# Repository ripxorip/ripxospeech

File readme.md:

# Ripxovoice

## Description

This readme is a WIP.

## Getting Started

### Dependencies

List any dependencies that need to be installed for this software to work. For example:

- Dependency 1
- Dependency 2

### Setup

(2024/01/07) This way of connecting everything is now deprecated. I am now using physical USB audio interfaces that gets passthrough to each virtual machine. This way I have a lot simpler streaming setup as I only need to stream from my workstation to a node which feeds line level audio to each audio interface.The next step is to create a desktop application which manages the actual part that runs on the workstation, unifying both the audio streaming and managing how keystrokes gets sent. Some current ideas I have includes:

- Being able to switch between English and Swedish using a button in a GUI.
    - Done by the workstation figuring out if Windows is in English or Swedish mode currently using a screenshot or something similar.

Currently (2023/12/17) setup everything accordingly:
(Note: There is no longer any need for running the audio from the VM host, voiceboxlinux also manages the routing to Windows using 192.168.122.xxx)

- In voiceboxlinux start Jacktrip: `PIPEWIRE_LATENCY="1024/48000" jacktrip -s`
- In Windows:
    - Start qjackctl (Pinned on the taskbar)
- In Windows:
    - Start Jacktrip (from terminal): `.\jacktrip.exe -c 192.168.122.137`
- In voiceboxlinux start the server: `./linux_gstreamer_server/serve_dest.sh`
- Route audio from client (can be any client)
- In voiceboxlinux Manually route the audio according to this screenshot: 

## TODOs
- Update this readme..
- I have decided to not use Linux for the Talon slave, consequently I am going to use Windows for that as well.
  The next step is to be able to get those keyboard events from the same application which is currently being
  used to fetch the keyboard strokes from Windows 11 own speech to text service. This application is called
  win11_keysender and it is written in C#.

### Using

Instructions for how to use your project. For example:

- Step 1
- Step 2

## Contributing

Details about how other developers can contribute to your project.

## License

Information about the license your project uses.

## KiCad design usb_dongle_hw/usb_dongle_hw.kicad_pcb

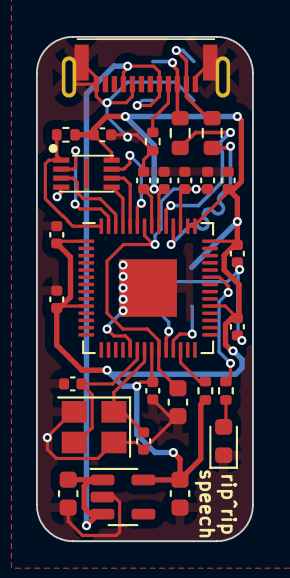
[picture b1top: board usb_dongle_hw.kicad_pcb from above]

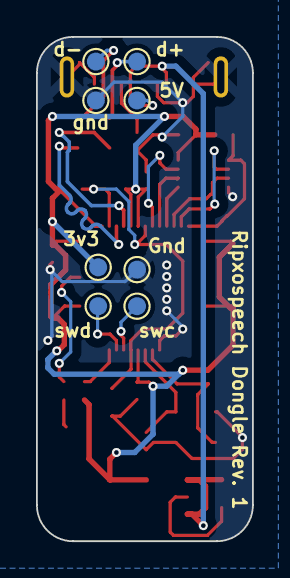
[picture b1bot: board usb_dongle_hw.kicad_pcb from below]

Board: 2 copper layers, 12.0 x 28.0 mm, 36 parts (8 on the bottom side), 22 nets.

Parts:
C1, C2: 12p; C_0402_1005Metric
C3, C5, C6, C7, C8, C9, C10, C11, C12, C13, C14: 0.1u; C_0402_1005Metric
C4: 1u; C_0603_1608Metric
C15, C16: 10uF; C_0603_1608Metric
D1: Blue; LED_0603_1608Metric
J1: PLUG-USBC-121SMT-4BS2S
R1: 1K; R_0402_1005Metric
R2: 470; R_0402_1005Metric
R3: 10K; R_0402_1005Metric
R4: 5.1k; R_0402_1005Metric
R5, R6: 27; R_0603_1608Metric
TP1, TP2, TP3, TP4, TP5, TP6, TP7, TP8: TestPoint; TestPoint_Pad_D1.0mm
U1: RP2040; QFN-56-1EP_7x7mm_P0.4mm_EP3.2x3.2mm
U2: W25Q64JV; SON50P300X200X60-9N
U3: AP2112K-3.3; SOT-23-5
Y1: 12Mhz; Crystal_SMD_3225-4Pin_3.2x2.5mm

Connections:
+1V1: C3.1, C4.1, C5.1, U1.23 (DVDD), U1.45 (VREG_VOUT), U1.50 (DVDD)
+3V3: C6.1, C7.1, C8.1, C9.1, C10.1, C11.1, C12.1, C13.1, C14.1, C16.1, R1.1, R3.2, TP1.1, U1.1 (IOVDD), U1.10 (IOVDD), U1.22 (IOVDD), U1.33 (IOVDD), U1.42 (IOVDD), U1.43 (ADC_AVDD), U1.44 (VREG_IN), U1.48 (USB_VDD), U1.49 (IOVDD), U2.8 (VDD), U3.5 (VOUT)
+5V: C15.1, J1.A04, J1.B09, TP7.1, U3.1 (VIN), U3.3 (EN)
/usb-d+: R5.2, U1.47 (USB_D+)
/usb-d-: R6.2, U1.46 (USB_D-)
GND: C1.1, C2.1, C3.2, C4.2, C5.2, C6.2, C7.2, C8.2, C9.2, C10.2, C11.2, C12.2, C13.2, C14.2, C15.2, C16.2, D1.1 (K), J1.A01, J1.A12, J1.B12, J1.Gnd, R4.1, TP2.1, TP8.1, U1.19 (TESTEN), U1.57 (GND), U2.4 (GND), U3.2 (GND), Y1.2, Y1.4
unnamed: D1.2 (A), R2.1
unnamed: J1.A05, R4.2
unnamed: R2.2, U1.37 (GPIO25)
unnamed: R1.2, U1.26 (RUN)
unnamed: C1.2, U1.20 (XIN), Y1.3
unnamed: C2.2, U1.21 (XOUT), Y1.1
QSPI_CS: R3.1, U1.56 (QSPI_SS), U2.1 (~CS)
QSPI_SCLK: U1.52 (QSPI_SCLK), U2.6 (SCK)
QSPI_SD0: U1.53 (QSPI_SD0), U2.5 (DI/IO0)
QSPI_SD1: U1.55 (QSPI_SD1), U2.2 (DO/IO1)
QSPI_SD2: U1.54 (QSPI_SD2), U2.3 (~WP/IO2)
QSPI_SD3: U1.51 (QSPI_SD3), U2.7 (~HOLD/IO3)
SWCLK: TP4.1, U1.24 (SWCLK)
SWDIO: TP3.1, U1.25 (SWD)
USB_d+: J1.A06, R5.1, TP5.1
USB_d-: J1.A07, R6.1, TP6.1

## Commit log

2023-10-20 feat: Initial commit
2023-10-21 feat: Adds pip reqs
2023-10-21 feat: Adds table to translate the xev keycodes to name
2023-10-22 feat: Adds translation to HID report, next up colemak translation
2023-10-22 feat: Adds initial function to convert keycodes to colemak dh
2023-10-22 feat: Adds initial version of the key_presser class, managed to get some keys pressed (full chain using aplay instead of a soundcard though)
2023-10-22 fix: Colemak mappings
2023-10-22 Adds support for modifier keys
2023-10-24 feat: Adds setup/teardown script for pipewire pipeline
2023-10-27 feat: Changes from http to raw UDP sockets
2023-10-27 feat: removes flask
2023-10-27 wip: Scripting refactoring
2023-10-27 feat: Adds support for switching using a script
2023-10-27 fix: removes not needed scripts
2023-11-03 feat: Disables pulseaudio native module, will use gstreamer instead
2023-11-03 fix: Syntax error
2023-11-03 feat: WIP for python script for routing
2023-11-08 feat: Tmux seems promising
2023-11-09 feat: Adds support for Gstreamer accelerated talon
2023-11-10 feat: Pulse/pipewire routing for Windows VM (neet to tune latency somewhere)
2023-11-12 feat: Adds support for sending text messages from run.py (fk route.py)
2023-11-12 fix: Param not needed anymore
2023-11-12 fix: Naming
2023-11-13 feat: Adds python script which sends to clipboard, (dummy solution)
2023-11-13 wip: Win11 + testing
2023-11-14 feat: Unified stream for both backends
2023-11-14 feat: Adds support for sending strings to the ripxovoice devices
2023-11-14 feat: Adds support for client to read HID data
2023-11-15 wip: HID commands
2023-11-16 feat: Adds the rest of the HID commands
2023-11-16 feat: Client HID commands
2023-11-17 fix: typo
2023-11-25 feat: Consolidation with the other two project
2023-11-25 feat: Initial commit for the OCR stuff
2023-11-25 feat: Adds polling
2023-11-25 feat: Focus the application when starting dictation
2023-11-25 feat: OCR reacts to data on 5005
2023-11-25 feat: Adds HID for gdocs
2023-11-25 HID on client as well
2023-11-25 feat: Ready for actual logic (see Form1.cs)
2023-11-27 fix: Not needed files
2023-11-27 feat: First working version
2023-12-01 feat: Adds Gstreamer Server for Windows
2023-12-01 chore: Renaming
2023-12-01 feat: Queues and not killing servers
2023-12-01 Update the gst path for Win
2023-12-01 fix: Win ip
2023-12-01 fix: Temporarily disable Linux app switching, bug?
2023-12-01 feat: Adds python script for routing, might be needed when tear down not working on windows
2023-12-02 feat: Refactoring to ripxospeech.py instead of run.py
2023-12-02 chore: more refactoring
2023-12-02 chore: first part of the refactoring of the server
2023-12-02 chore: continued refactoring to enable more backends for sending the keystrokes
2023-12-02 chore: more refectoring
2023-12-02 feat: add to support so that the dictation is automatically stopped when changing language
2023-12-02 chore: refactored away that part that has to do with commands from the keyboard server
2023-12-07 feat: Gst server from python + flake
2023-12-08 feat: Adds win11 pcm scaffolding
2023-12-08 feat: Adds support for vscode build
2023-12-08 feat: VSCode task for server and python client (needs to be rewritten)
2023-12-08 feat: Task for running the client as well
2023-12-09 feat: New audio setup (gst + jack)
2023-12-09 fix: Env
2023-12-09 fix: Env so that it works on both nix and other distros
2023-12-11 feat: Initial scaffolding with inspiration from the magslide_firmware (controller)
2023-12-14 feat: Add nix derivation for the embedded firmware of the USB dongle
2023-12-16 feat: Adds support for resetting the embedded dongle (send 0x66) and scaffolding for receiving HID data
2023-12-16 feat: add support for flashing the dongle from the main script
2023-12-16 feat: First working version! Need to understand where the latency is coming from, but anyway it works.
2023-12-17 feat: Fixes the latency issues. Ready for review
2023-12-17 feat: Adds support for routing local audio
2023-12-17 Add support for USB dongle (RP2040) (#1)
    * feat: Initial scaffolding with inspiration from the magslide_firmware (controller)
    * feat: Add nix derivation for the embedded firmware of the USB dongle
    * feat: Adds support for resetting the embedded dongle (send 0x66) and scaffolding for receiving HID data
    * feat: add support for flashing the dongle from the main script
    * feat: First working version! Need to understand where the latency is coming from, but anyway it works.
    * feat: Fixes the latency issues. Ready for review
2023-12-17 feat: Add support for blinking the LED when transmitting keyboard strokes from the USB dongle
2023-12-17 feat: voiceboxlinux is now audio master, not ripxolab
2024-01-07 feat: New architecture, pi to pi and sound cards for the VMs
2024-01-07 feat: Updates to read me file to include some ideas I have for the future
2024-01-07 fix: fixes broken key up
2024-01-07 Fixes apostrophe
2024-01-08 feat: Initial commit (build using nix develop nix develop .#ripxospeech_gtk -c $SHELL and start code from there
2024-01-08 feat: Adds my name as dev
2024-01-11 feat: Python instead of C for GUI
2024-01-14 fix: moves silk
2024-01-14 feat: DRC pass, routing complete
2024-01-14 fix: Silk
2024-01-15 feat: This goes into JLCPCB production
2024-01-15 feat: Adds support for starting/stopping the client stream. The same shall be done for the audio server (Rpi) use setsid etc when wrapping to a socket server.
2024-01-16 feat: Adds socket server for starting/stoping the gst server
2024-01-16 feat: Start/stop the gst server when pushing the button
2024-01-16 fix: Proctects against multiple starts
2024-01-16 feat: Adds support for starting/stopping audio stream when a key is pushed from Gnome/Pi
2024-01-16 feat: Style using CSS example
2024-01-16 wip: UI
2024-01-17 feat: GUI Structure
2024-01-17 feat: GUI Makeup
2024-01-17 feat: Buttons connected
2024-01-17 feat: Adds stop button, next step is dongle status and then changing language
2024-01-17 feat: Dongle status
2024-01-17 feat: Clean status text
2024-01-17 feat: Adds convenience script for starting the current GUI
2024-01-17 wip: Win lang switching, will be a screenshot with Python OCR and TCP instead
2024-01-18 feat: Adds support for changing lang
2024-01-18 feat: Able to change Win language using OCR
2024-01-18 fix: Ignored image
2024-01-18 fix: Adds error handling if I get a bad message.
2024-01-19 feat: Adds support for virtual keyboard without any dongles
2024-01-20 chore: Virtual keyboard cleanup
2024-01-21 feat: Adds code server for Talon config
2024-01-21 feat: Open Talon config from GUI, OBS: Im sick as a dog so this and the previous commits needs to be checked when Im back on my feet again
2024-01-22 fix: Commands kept on haning, doing it the python way instead
2024-01-22 fix: send_string to bytes
2024-01-27 feat: Input commands cleanup
2024-01-27 feat: Adds server side support for åä and ö
2024-01-27 feat: Adds fn keys as generic actions rather than hard coded actions (more flexible this way)
2024-01-27 Restarts the app on language switching through the debugger
2024-01-27 feat: Fully working language switching for windows
2024-01-27 feat: Adds Doublethink class for preprocessing, undo/redo and inline editing using voice
2024-01-28 feat: The doublethink can now parse the text and repack it afterwards
2024-01-28 feat: initial, see logseq bugs
2024-01-29 fix: Protect against hidraw not existing, next up gst missing on vanila system
2024-01-29 fix: Adds missing gstreamer
2024-01-30 feat: Proper killing
2024-01-30 wip: Test scaffoliding
2024-03-10 fix: This test clearly proves that there is nothing wrong when sending bursts of messages, rather the error is somewhere in the doublethink code
2024-03-11 WIP: Audio latency test WIP
2024-03-11 feat: First working version of the audio latency test sequence
2024-03-11 feat: Now saves the recording for future reference
2024-03-12 feat: Adds combined stream script
2024-03-20 feat: adds testing script for local raspberry pi
2024-03-30 feat: Initial commit of the gateway, can now stream a sine in realtime
2024-03-31 feat: Async alsa playback
2024-03-31 fix: Cleanup
2024-03-31 feat: Initial commit of the client
2024-04-14 wip: Audio gateway
2024-04-14 wip: audio client
2024-04-14 feat: Test with select instead of separate thread
2024-04-14 feat: First working version, although a bit naive perhaps, need to figure out what happens when loosing sync etc
2024-04-14 fix: Yet another copliot bug
2024-04-15 feat: Adds USB soundcard prober (for finding the master device among the three identical USB dongles)
2024-04-16 feat: XML format for device detection
2024-06-14 feat: Gateway uses pipewire instead
2024-06-14 wip: Working streame on localhost
2024-06-14 Cleanup and adds new sources for the buffer/sync functions
2024-06-14 chore: Removes not needed struct
2024-06-14 feat: Adds unittest
2024-06-14 feat: Test when in sync, next up add a buffer
2024-06-14 feat: Adds ring_buffer
2024-06-14 feat: Adds mutex, shall be used for the ring_buffer_t
2024-06-14 feat: Proper mutex + extended tests
2024-06-14 feat: Adds actions for underrun and overrun
2024-06-14 fix: Buffer size for the receiver
2024-06-14 feat: Adds proper IP
2024-06-14 feat: Adds test mode
2024-06-14 fix: Test mode disabled by default
2024-06-21 feat: Removes Doublethink, removes audio streaming start/stop
2024-06-21 wip: Talon Win
2024-06-21 feat: Windows Talon Mode
2024-06-21 feat: Now using Windows as well for Talon
2024-06-22 fix: More keys Win
2024-06-22 Update Form1.cs
    feat: Basic support for dumb undo
2024-06-22 feat: Hard codes the windows input to Swedish, makes sure that talon is handled in english.
2024-06-22 feat: Adds lazy switching
2024-08-26 fix: Revert always swedish win 11
2024-08-26 feat: Adds support for queuing up messages if there's not yet a full buffer
